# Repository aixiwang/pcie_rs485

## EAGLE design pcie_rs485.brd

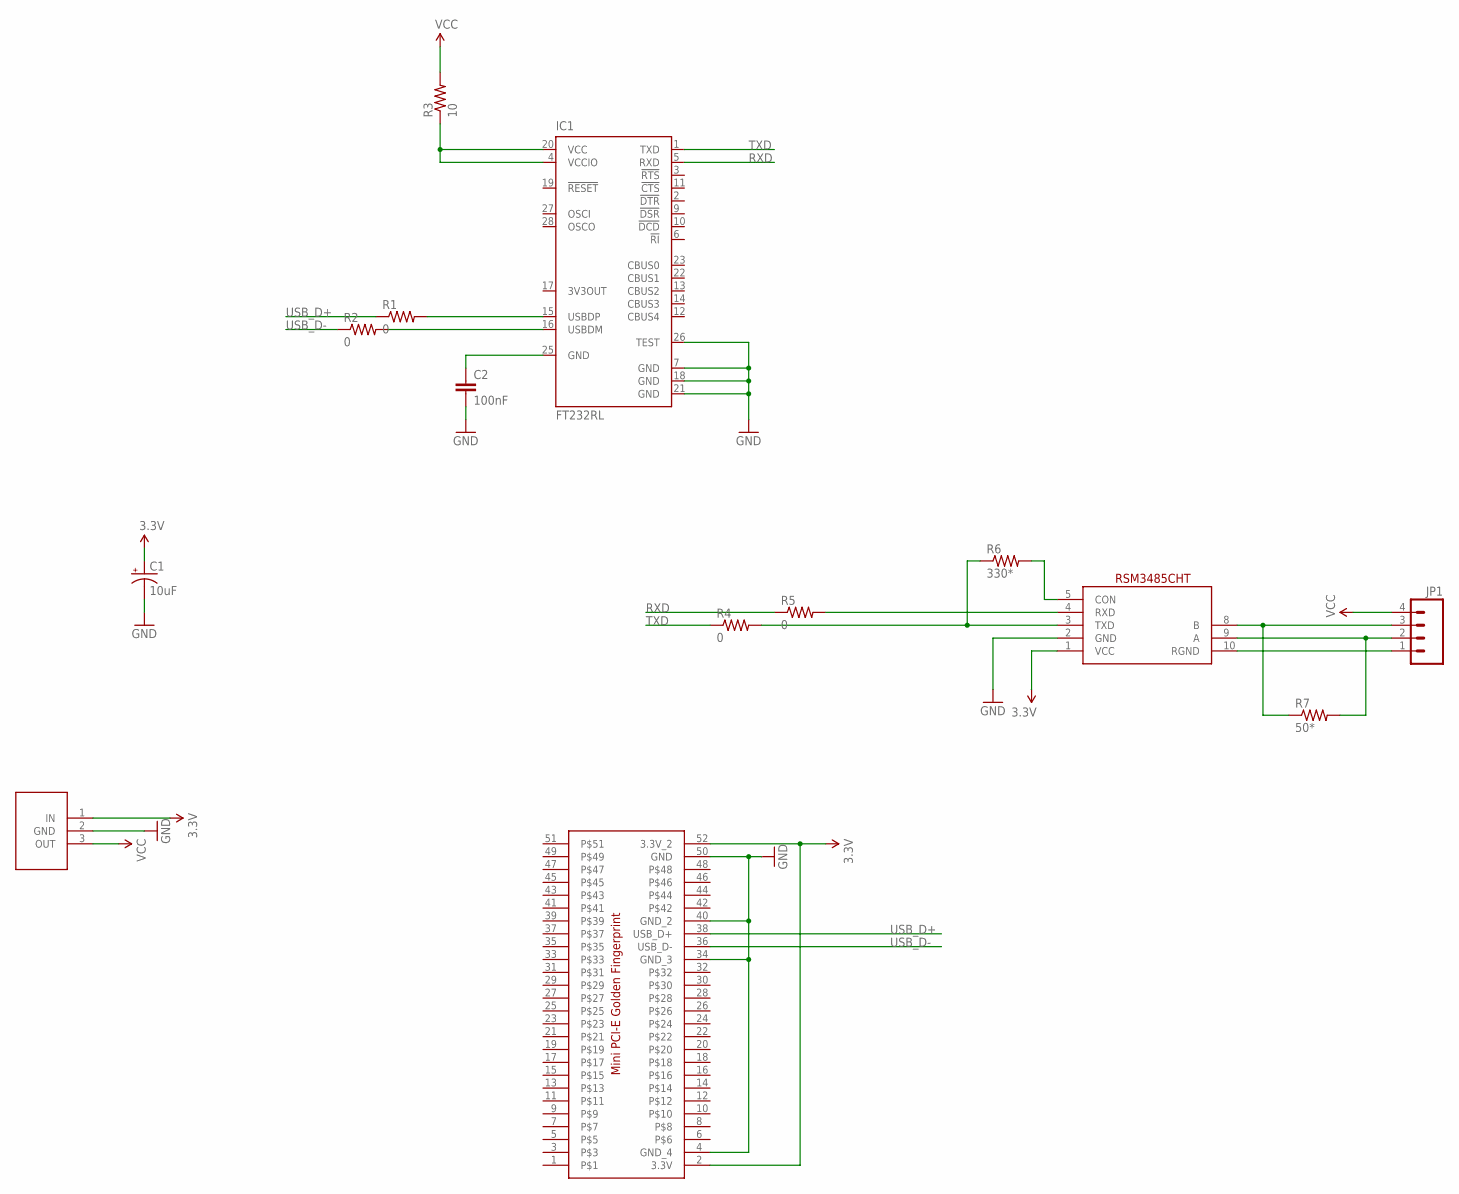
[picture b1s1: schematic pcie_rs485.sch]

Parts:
C1: 10uF; EIA3216
C2: 100nF; 0603-CAP
IC1: FT232RL; SSOP28
JP1: M04PTH; 1X04
NC1: RSM3485CHT
R1, R2, R4, R5: 0; 0603-RES
R3: 10; 0603-RES
R6: 330*; 0603-RES
R7: 50*; 0603-RES
U1: MINI_PCIE_MODULE; MINI_PCIE
U?1: BL8530_M_V5.0; BL8530_M

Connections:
3.3V: C1.A (+), NC1.1 (VCC), U1.2 (3.3V), U1.52 (3.3V_2), U?1.1 (IN)
GND: C1.C (-), C2.2, IC1.7 (GND), IC1.18 (GND), IC1.21 (GND), IC1.26 (TEST), NC1.2 (GND), U1.4 (GND_4), U1.34 (GND_3), U1.40 (GND_2), U1.50 (GND), U?1.2 (GND)
unnamed: IC1.15 (USBDP), R1.2
unnamed: IC1.16 (USBDM), R2.2
unnamed: C2.1, IC1.25 (GND)
unnamed: NC1.5 (CON), R6.2
RS485_A: JP1.2, NC1.9 (A), R7.2
RS485_B: JP1.3, NC1.8 (B), R7.1
RS485_RGND: JP1.1, NC1.10 (RGND)
RXD: IC1.5 (RXD), R5.1
RXD_1: NC1.4 (RXD), R5.2
TXD: IC1.1 (TXD), R4.1
TXD_1: NC1.3 (TXD), R4.2, R6.1
USB_D+: R1.1, U1.38 (USB_D+)
USB_D-: R2.1, U1.36 (USB_D-)
VCC: JP1.4, R3.2, U?1.3 (OUT)
VCC_1: IC1.4 (VCCIO), IC1.20 (VCC), R3.1

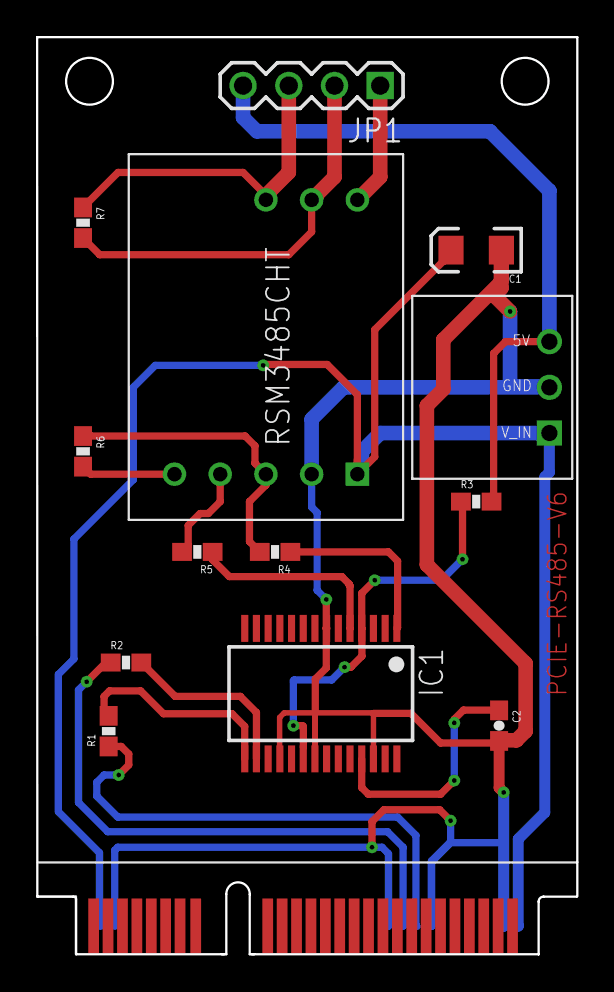
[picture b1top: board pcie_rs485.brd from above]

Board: 2 copper layers, 30.0 x 51.0 mm, 14 parts (0 on the bottom side), 17 nets.

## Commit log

2018-01-14 first checkin

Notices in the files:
parts and their libraries:
SparkFun-Capacitors: Licensing: CC v3.0 Share-Alike You are welcome to use this library for commercial purposes.
